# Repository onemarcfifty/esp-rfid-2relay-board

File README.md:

# esp-rfid-2relay-board
a two relay board for use with esp-rfid and a Wiegand RFID keypad

This is a simple board that I have designed to open my two garage doors. It is using an ESP8266 processor and running the ESP-RFID firmware. Please check the videos on my youtube channel for more details:

[Designing the board](https://youtu.be/ah8-FsuAJAM)
[milling the board with the CNC router](https://youtu.be/63Tgc9mA8FI)

Find more videos on [my youtube channel](https://www.youtube.com/channel/UCG5Ph9Mm6UEQLJJ-kGIC2AQ)

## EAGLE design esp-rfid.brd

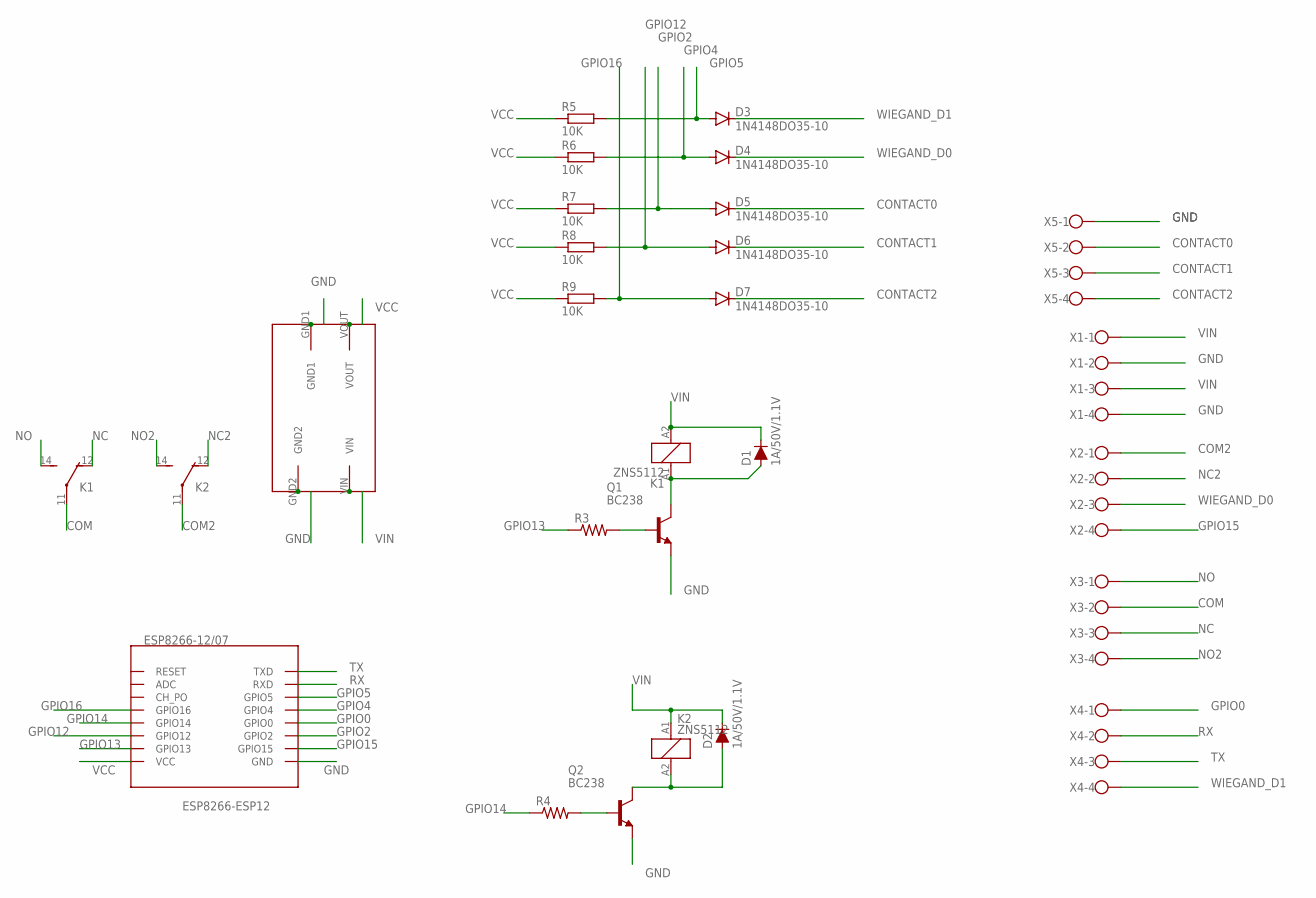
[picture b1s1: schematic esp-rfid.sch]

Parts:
D1, D2: 1A/50V/1.1V; DIODE-1N4001
D3, D4, D5, D6, D7: 1N4148DO35-10; DO35-10
K1, K2: ZNS5112; ZN5
Q1, Q2: BC238; TO92
R3, R4: AXIAL-0.3
R5, R6, R7, R8, R9: 10K; 0207/10
U$1: ESP8266-ESP12; ESP8266-12
U$2: LM2596-DC-DC-STEPDOWN-BOARD; STEPDOWN-CONVERTER
X1, X2, X3, X4, X5: W237-4

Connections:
COM: K1.11, X3.2
COM2: K2.11, X2.1
CONTACT0: D5.C, X5.2
CONTACT1: D6.C, X5.3
CONTACT2: D7.C, X5.4
GND: Q1.1 (E), Q2.1 (E), U$1.GND, U$2.GND1, U$2.GND2, X1.2, X1.4, X5.1
GPIO0: U$1.IO0 (GPIO0), X4.1
GPIO2: D5.A, R7.2, U$1.IO2 (GPIO2)
GPIO4: D4.A, R6.2, U$1.IO4 (GPIO4)
GPIO5: D3.A, R5.2, U$1.IO5 (GPIO5)
GPIO12: D6.A, R8.2, U$1.IO12 (GPIO12)
GPIO13: R3.P$1 (1), U$1.IO13 (GPIO13)
GPIO14: R4.P$1 (1), U$1.IO14 (GPIO14)
GPIO15: U$1.IO15 (GPIO15), X2.4
GPIO16: D7.A, R9.2, U$1.IO16 (GPIO16)
unnamed: Q2.2 (B), R4.P$2 (2)
unnamed: D1.A, K1.A1 (1), Q1.3 (C)
unnamed: D2.A, K2.A2 (2), Q2.3 (C)
unnamed: Q1.2 (B), R3.P$2 (2)
NC: K1.12 (O), X3.3
NC2: K2.12 (O), X2.2
NO: K1.14 (S), X3.1
NO2: K2.14 (S), X3.4
RX: U$1.RX (RXD), X4.2
TX: U$1.TX (TXD), X4.3
VCC: R5.1, R6.1, R7.1, R8.1, R9.1, U$1.VCC, U$2.VOUT
VIN: D1.C, D2.C, K1.A2 (2), K2.A1 (1), U$2.VIN, X1.1, X1.3
WIEGAND_D0: D4.C, X2.3
WIEGAND_D1: D3.C, X4.4

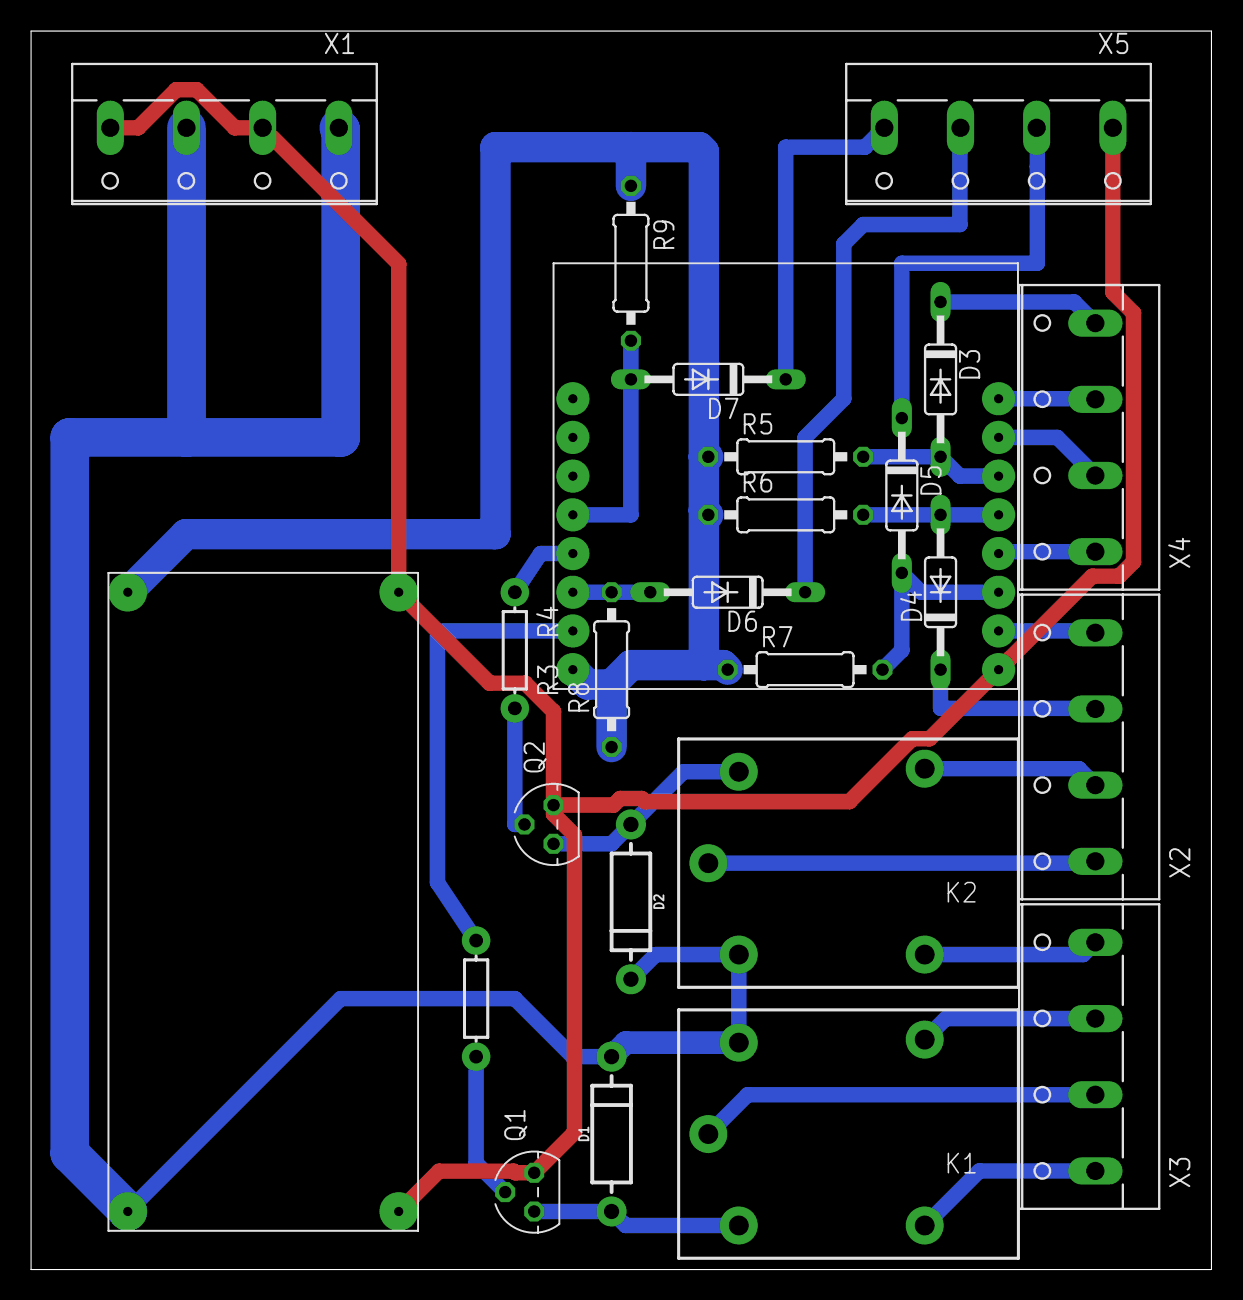
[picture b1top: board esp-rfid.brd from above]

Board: 2 copper layers, 77.5 x 81.2 mm, 25 parts (0 on the bottom side), 29 nets.

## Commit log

2020-10-06 initial upload
2020-10-20 adding images
2020-10-20 changed image resolution

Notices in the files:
parts and their libraries:
SparkFun-DiscreteSemi: Licensing: Creative Commons ShareAlike 4.0 International - https://creativecommons.org/licenses/by-sa/4.0
